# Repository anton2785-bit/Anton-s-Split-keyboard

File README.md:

# Anton-s-Split-keyboard
---
# BOM
* 2x XIAO nRF52840 SMD ( the microcontrollers )
* 40x MX-Style switches ( preferably black or red)
* 40x Black keykaps
* 40x diodes
* 3x mini LEDs
* 2x Batteries
* 1x Rotary encoder
* The 2 difrent case parts
* The 2 PCBs
---
# Images
* This image inspired me for the layout for the keyboard

* These are both sides of the keyboard in the shematic tab in kicad

* This is the final PCB wiring

* and the 3d models of it

* This is the case, that i made

* And this is the whole assembly

---
# Instructions of how to assemble
* First solder all of the diodes, keyboard switches, LEDs, Microcontrollers and batteries
* Second place the now assembled PCB in the case and connect it to a computer via USB C cable
* Third you need to upload the Firmware on the microcontrollers
* And finally you need to put all of the keycaps and test the keyboard

---
# Use Cases
- Expanding my hands-on experience with hardware by designing more advanced PCBs and practicing soldering.
- Challenging myself to improve typing speed and ergonomics by adapting to different keyboard layouts.

---
# Credits

Designed and built by (Anton/ Anton-2785-bit) Inspired by open‑source mechanical keyboard and hackpad communities (https://blueprint.hackclub.com/home).

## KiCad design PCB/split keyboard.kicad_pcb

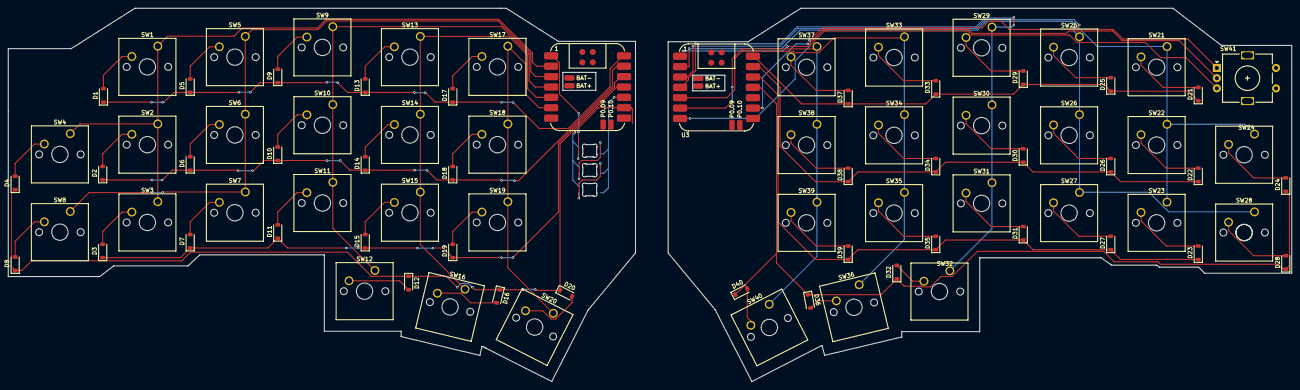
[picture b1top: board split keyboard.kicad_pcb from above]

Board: 2 copper layers, 314.2 x 91.3 mm, 86 parts (0 on the bottom side), 65 nets.

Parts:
D1, D2, D3, D4, D5, D6, D7, D8, D9, D10, D11, D12, D13, D14, D15, D16, D17, D18, D19, D20, D21, D22, D23, D24, D25, D26, D27, D28, D29, D30, D31, D32, D33, D34, D35, D36, D37, D38, D39, D40: D; D_SOD-123
D41, D42, D43: SK6812MINI-E; MX_SK6812MINI-E_REV
SW1, SW2, SW3, SW4, SW5, SW6, SW7, SW8, SW9, SW10, SW11, SW12, SW13, SW14, SW15, SW16, SW17, SW18, SW19, SW20, SW21, SW22, SW23, SW24, SW25, SW26, SW27, SW28, SW29, SW30, SW31, SW32, SW33, SW34, SW35, SW36, SW37, SW38, SW39, SW40: SW_Push; SW_Cherry_MX_1.00u_PCB
SW41: RotaryEncoder_Switch; RotaryEncoder_Alps_EC11E-Switch_Vertical_H20mm
U1, U3: XIAO-nRF52840-SMD; Xiao_nRF52840_AC_Reflow

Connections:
GND: D41.3 (VSS), D42.3 (VSS), D43.3 (VSS), SW41.C, U1.13 (GND), U3.13 (GND)
unnamed: D1.2 (A), SW1.2
unnamed: D1.1 (K), D5.1 (K), D9.1 (K), D13.1 (K), D17.1 (K), U1.8 (P1.12_D7_RX)
unnamed: D2.2 (A), SW2.2
unnamed: D3.2 (A), SW3.2
unnamed: D4.2 (A), SW4.2
unnamed: D5.2 (A), SW5.2
unnamed: D6.2 (A), SW6.2
unnamed: D7.2 (A), SW7.2
unnamed: D8.2 (A), SW8.2
unnamed: D9.2 (A), SW9.2
unnamed: D10.2 (A), SW10.2
unnamed: D2.1 (K), D6.1 (K), D10.1 (K), D14.1 (K), D18.1 (K), U1.9 (P1.13_D8_SCK)
unnamed: D11.2 (A), SW11.2
unnamed: D3.1 (K), D7.1 (K), D11.1 (K), D15.1 (K), D19.1 (K), U1.10 (P1.14_D9_MISO)
unnamed: D12.2 (A), SW12.2
unnamed: D4.1 (K), D8.1 (K), D12.1 (K), D16.1 (K), D20.1 (K), U1.11 (P1.15_D10_MOSI)
unnamed: D13.2 (A), SW13.2
unnamed: D14.2 (A), SW14.2
unnamed: D15.2 (A), SW15.2
unnamed: D16.2 (A), SW16.2
unnamed: D17.2 (A), SW17.2
unnamed: D18.2 (A), SW18.2
unnamed: D19.2 (A), SW19.2
unnamed: D20.2 (A), SW20.2
unnamed: D21.2 (A), SW21.2
unnamed: D21.1 (K), D25.1 (K), D29.1 (K), D33.1 (K), D37.1 (K), U3.8 (P1.12_D7_RX)
unnamed: D22.2 (A), SW22.2
unnamed: D22.1 (K), D26.1 (K), D30.1 (K), D34.1 (K), D38.1 (K), U3.9 (P1.13_D8_SCK)
unnamed: D23.2 (A), SW23.2
unnamed: D23.1 (K), D27.1 (K), D31.1 (K), D35.1 (K), D39.1 (K), U3.10 (P1.14_D9_MISO)
unnamed: D24.2 (A), SW24.2
unnamed: D24.1 (K), D28.1 (K), D32.1 (K), D36.1 (K), D40.1 (K), U3.11 (P1.15_D10_MOSI)
unnamed: D25.2 (A), SW25.2
unnamed: D26.2 (A), SW26.2
unnamed: D27.2 (A), SW27.2
unnamed: D28.2 (A), SW28.2
unnamed: D29.2 (A), SW29.2
unnamed: D30.2 (A), SW30.2
unnamed: D31.2 (A), SW31.2
unnamed: D32.2 (A), SW32.2
unnamed: D33.2 (A), SW33.2
unnamed: D34.2 (A), SW34.2
unnamed: D35.2 (A), SW35.2
unnamed: D36.2 (A), SW36.2
unnamed: D37.2 (A), SW37.2
unnamed: D38.2 (A), SW38.2
unnamed: D39.2 (A), SW39.2
unnamed: D40.2 (A), SW40.2
unnamed: D41.4 (DIN), U1.1 (P0.02_A0_D0)
unnamed: D41.2 (DOUT), D42.4 (DIN)
unnamed: D41.1 (VDD), D42.1 (VDD), D43.1 (VDD), U1.12 (3V3)
unnamed: D42.2 (DOUT), D43.4 (DIN)
unnamed: SW1.1, SW2.1, SW3.1, SW4.1, U1.2 (P0.03_A1_D1)
unnamed: SW13.1, SW14.1, SW15.1, SW16.1, U1.5 (P0.04_A4_D4_SDA)
unnamed: SW17.1, SW18.1, SW19.1, SW20.1, U1.6 (P0.05_A5_D5_SCL)
unnamed: SW5.1, SW6.1, SW7.1, SW8.1, U1.3 (P0.28_A2_D2)
unnamed: SW9.1, SW10.1, SW11.1, SW12.1, U1.4 (P0.29_A3_D3)
unnamed: SW41.B, U3.1 (P0.02_A0_D0)
unnamed: SW21.1, SW22.1, SW23.1, SW24.1, U3.2 (P0.03_A1_D1)
unnamed: SW33.1, SW34.1, SW35.1, SW36.1, U3.5 (P0.04_A4_D4_SDA)
unnamed: SW37.1, SW38.1, SW39.1, SW40.1, U3.6 (P0.05_A5_D5_SCL)
unnamed: SW25.1, SW26.1, SW27.1, SW28.1, U3.3 (P0.28_A2_D2)
unnamed: SW29.1, SW30.1, SW31.1, SW32.1, U3.4 (P0.29_A3_D3)
unnamed: SW41.A, U3.7 (P1.11_D6_TX)

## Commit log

2026-02-04 File update
2026-02-04 Update README with images and descriptions
    Added images and descriptions for keyboard layout, PCB schematics, wiring, and assembly.
2026-02-04 Update README with use cases and credits
    Added a use case section and updated credits.
2026-02-04 Update component list in README.md
    Corrected item counts and added new components.
